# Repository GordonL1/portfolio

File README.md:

# Gordon's Portfolio
Basic portfolio with some of my recent projects and other prorgamming/computer things I have worked on recently

# Current Projects
Currently I'm working on writing a basic operating system + shell in Rust. I'm using a tutorial from os.phil-opp.com to get started, but I'd like to reimplement my programming language interpreter so that my OS can run prorgams in my prgramming language.

# Future Projects
I plan on expanding my programming langauge, making it more user friendly, implementing things lists, and adding more built in functions.
I also plan on making an interpeter for an array language I create (like Dyalog APL, BQN, J, or K).

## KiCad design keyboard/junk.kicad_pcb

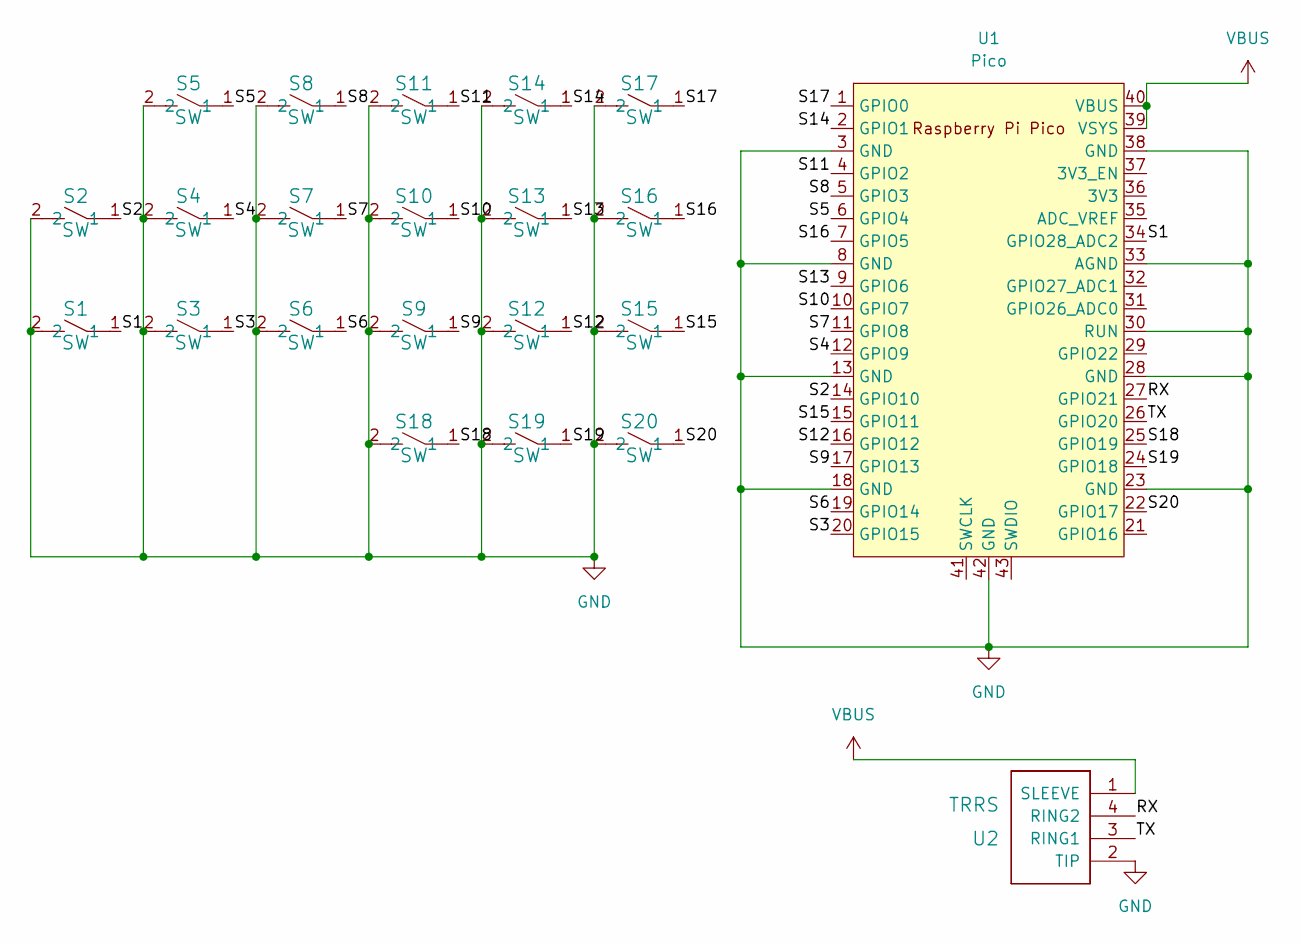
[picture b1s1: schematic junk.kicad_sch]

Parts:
S1, S2, S3, S4, S5, S6, S7, S8, S9, S10, S11, S12, S13, S14, S15, S16, S17, S18, S19, S20: SW; Kailh-PG1350-1u-reversible
U1: Pico; RPi_Pico_SMD_TH
U2: TRRS; TRRS-PJ-320A-dual

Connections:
/RX: U1.27 (GPIO21), U2.4 (RING2)
/S1: S1.1, U1.34 (GPIO28_ADC2)
/S2: S2.1, U1.14 (GPIO10)
/S3: S3.1, U1.20 (GPIO15)
/S4: S4.1, U1.12 (GPIO9)
/S5: S5.1, U1.6 (GPIO4)
/S6: S6.1, U1.19 (GPIO14)
/S7: S7.1, U1.11 (GPIO8)
/S8: S8.1, U1.5 (GPIO3)
/S9: S9.1, U1.17 (GPIO13)
/S10: S10.1, U1.10 (GPIO7)
/S11: S11.1, U1.4 (GPIO2)
/S12: S12.1, U1.16 (GPIO12)
/S13: S13.1, U1.9 (GPIO6)
/S14: S14.1, U1.2 (GPIO1)
/S15: S15.1, U1.15 (GPIO11)
/S16: S16.1, U1.7 (GPIO5)
/S17: S17.1, U1.1 (GPIO0)
/S18: S18.1, U1.25 (GPIO19)
/S19: S19.1, U1.24 (GPIO18)
/S20: S20.1, U1.22 (GPIO17)
/TX: U1.26 (GPIO20), U2.3 (RING1)
GND: S1.2, S2.2, S3.2, S4.2, S5.2, S6.2, S7.2, S8.2, S9.2, S10.2, S11.2, S12.2, S13.2, S14.2, S15.2, S16.2, S17.2, S18.2, S19.2, S20.2, U1.3 (GND), U1.8 (GND), U1.13 (GND), U1.18 (GND), U1.23 (GND), U1.28 (GND), U1.30 (RUN), U1.33 (AGND), U1.38 (GND), U1.42 (GND), U2.2 (TIP)
VBUS: U1.39 (VSYS), U1.40 (VBUS), U2.1 (SLEEVE)

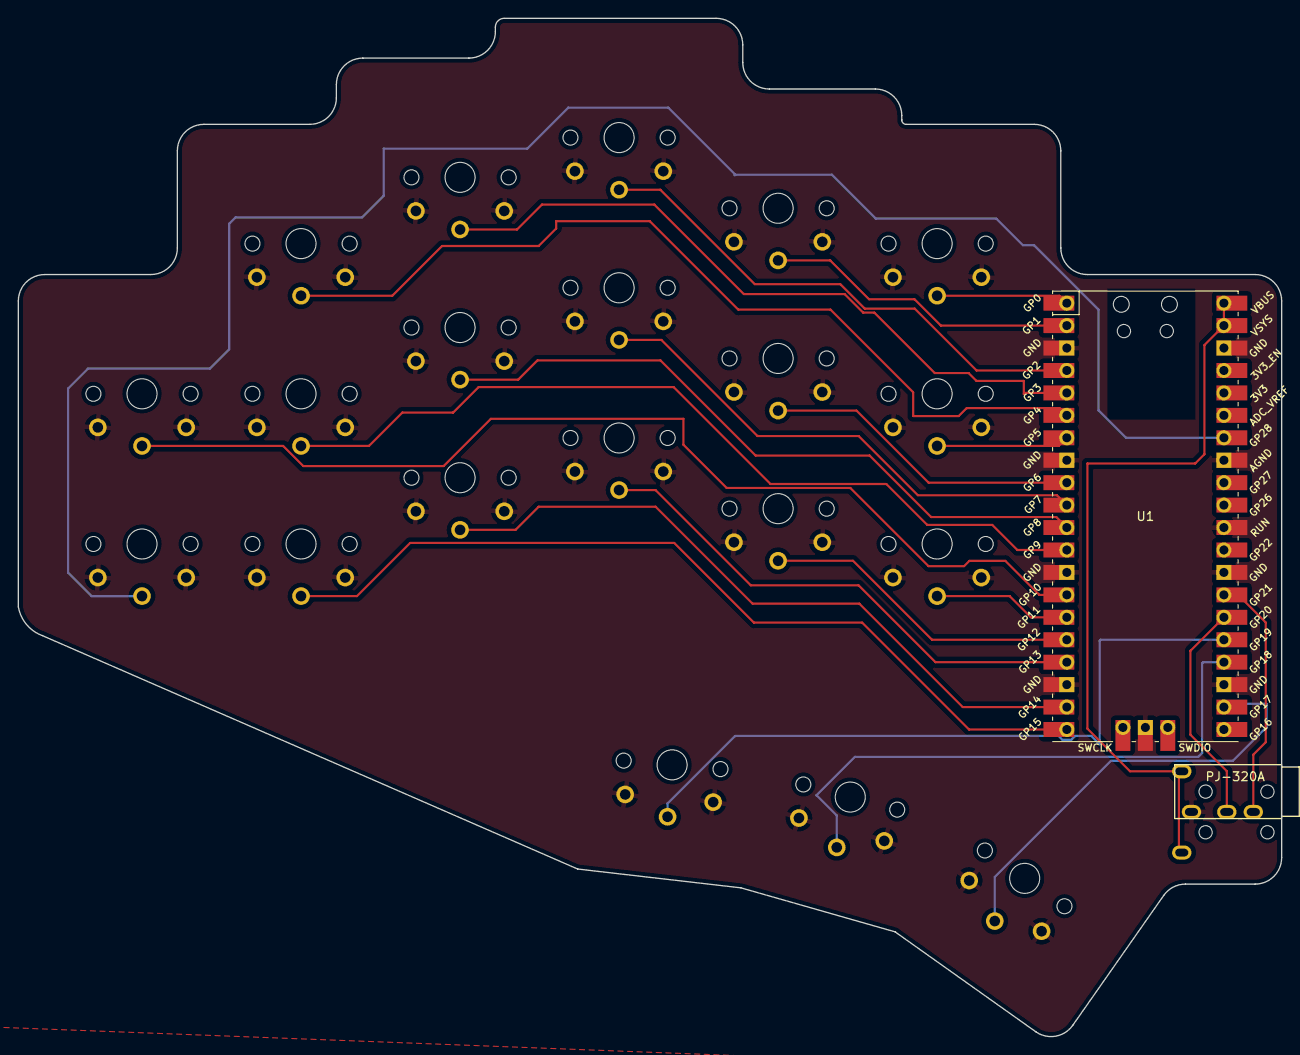
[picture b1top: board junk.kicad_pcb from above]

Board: 2 copper layers, 143.0 x 115.3 mm, 22 parts (0 on the bottom side), 24 nets.

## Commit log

2022-10-15 Added a bunch of files
    files
2022-10-15 Create about
2022-10-15 Added some more files
    files
